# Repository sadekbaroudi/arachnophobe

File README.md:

# arachnophobe

A 30 key column staggered board using the Seeed RP2040. Uses kailh hotswap and supports both Choc v1 and MX switches on the same pcb.

# Support me!

I have spent a lot of time and money designing prototypes, testing, developing, etc. Any contributions would be greatly appreciated!

If you don't want to, or can't afford to support me, please send me a message to let me know you've built one, along with pictures. Also, feel free to submit a pull request with pictures into this repository. I'd be happy to showcase your build.

Reddit: /u/sadekbaroudi
Discord: sadekbaroudi#1258

# Keymap

# Firmware

## QMK
[arachnophobe-qmk](https://github.com/sadekbaroudi/qmk_firmware/tree/master/keyboards/fingerpunch/arachnophobe)

Note that you may need to copy this folder into the latest develop branch (as of this writing, 2022-07-13) to get the RP2040 support in QMK.

## ZMK

[arachnophobe-zmk](https://github.com/sadekbaroudi/zmk-arachnophobe)

# Images

## PCB

## Choc build

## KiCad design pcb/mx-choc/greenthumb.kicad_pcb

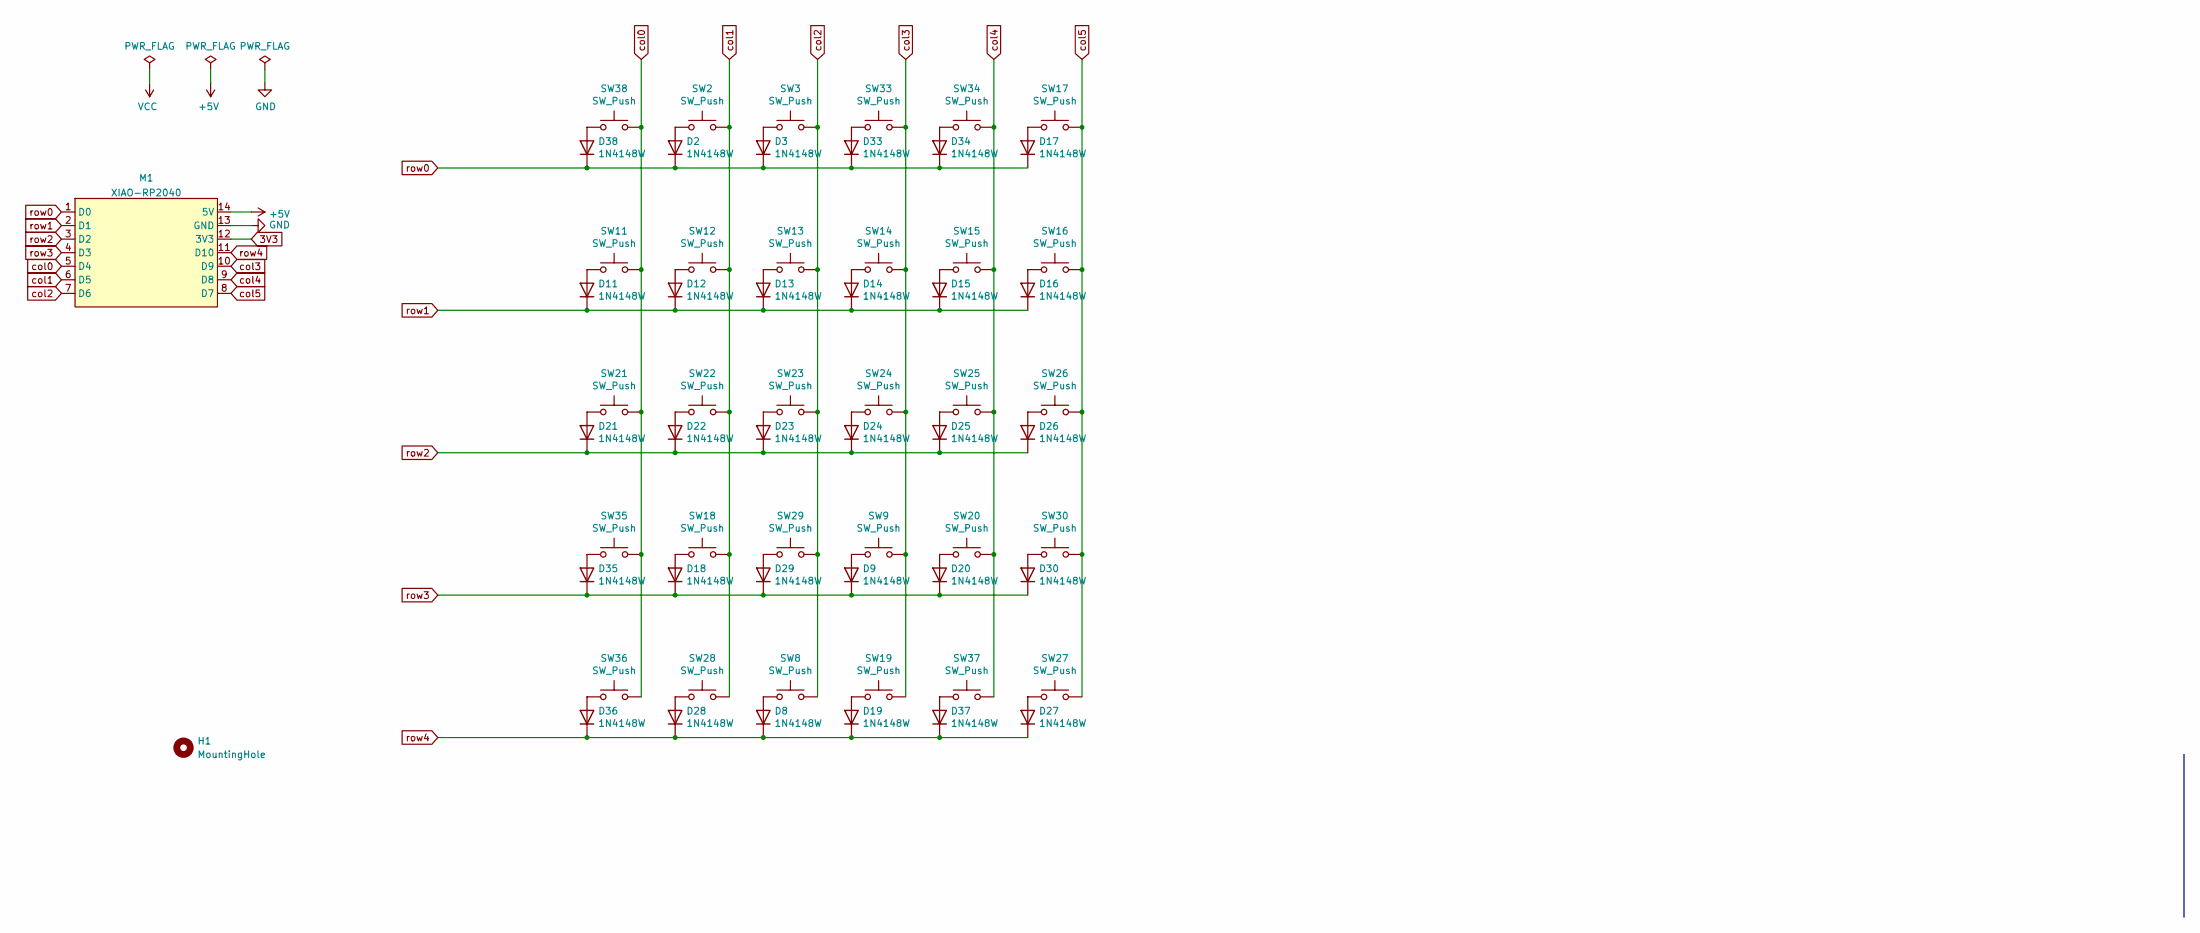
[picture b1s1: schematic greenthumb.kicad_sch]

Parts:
D2, D3, D8, D9, D11, D12, D13, D14, D15, D16, D17, D18, D19, D20, D21, D22, D23, D24, D25, D26, D27, D28, D29, D30, D33, D34, D35, D36, D37, D38: 1N4148W; D_SOD-123; LCSC C909967
H1: MountingHole; fingerpunch-logo
M1: XIAO-RP2040; LCSC 102010428
SW2, SW3, SW8, SW9, SW11, SW12, SW13, SW14, SW15, SW16, SW17, SW18, SW19, SW20, SW21, SW22, SW23, SW24, SW25, SW26, SW27, SW28, SW29, SW30, SW33, SW34, SW35, SW36, SW37, SW38: SW_Push; Kailh_socket_MX-ChocV1

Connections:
3V3: M1.12 (3V3)
+5V: M1.14 (5V)
GND: M1.13 (GND)
unnamed: D2.2 (A), SW2.1
unnamed: D3.2 (A), SW3.1
unnamed: D8.2 (A), SW8.1
unnamed: D9.2 (A), SW9.1
unnamed: D11.2 (A), SW11.1
unnamed: D12.2 (A), SW12.1
unnamed: D13.2 (A), SW13.1
unnamed: D14.2 (A), SW14.1
unnamed: D15.2 (A), SW15.1
unnamed: D16.2 (A), SW16.1
unnamed: D17.2 (A), SW17.1
unnamed: D18.2 (A), SW18.1
unnamed: D19.2 (A), SW19.1
unnamed: D20.2 (A), SW20.1
unnamed: D21.2 (A), SW21.1
unnamed: D22.2 (A), SW22.1
unnamed: D23.2 (A), SW23.1
unnamed: D24.2 (A), SW24.1
unnamed: D25.2 (A), SW25.1
unnamed: D26.2 (A), SW26.1
unnamed: D27.2 (A), SW27.1
unnamed: D28.2 (A), SW28.1
unnamed: D29.2 (A), SW29.1
unnamed: D30.2 (A), SW30.1
unnamed: D33.2 (A), SW33.1
unnamed: D34.2 (A), SW34.1
unnamed: D35.2 (A), SW35.1
unnamed: D36.2 (A), SW36.1
unnamed: D37.2 (A), SW37.1
unnamed: D38.2 (A), SW38.1
col0: M1.5 (D4), SW11.2, SW21.2, SW35.2, SW36.2, SW38.2
col1: M1.6 (D5), SW2.2, SW12.2, SW18.2, SW22.2, SW28.2
col2: M1.7 (D6), SW3.2, SW8.2, SW13.2, SW23.2, SW29.2
col3: M1.10 (D9), SW9.2, SW14.2, SW19.2, SW24.2, SW33.2
col4: M1.9 (D8), SW15.2, SW20.2, SW25.2, SW34.2, SW37.2
col5: M1.8 (D7), SW16.2, SW17.2, SW26.2, SW27.2, SW30.2
row0: D2.1 (K), D3.1 (K), D17.1 (K), D33.1 (K), D34.1 (K), D38.1 (K), M1.1 (D0)
row1: D11.1 (K), D12.1 (K), D13.1 (K), D14.1 (K), D15.1 (K), D16.1 (K), M1.2 (D1)
row2: D21.1 (K), D22.1 (K), D23.1 (K), D24.1 (K), D25.1 (K), D26.1 (K), M1.3 (D2)
row3: D9.1 (K), D18.1 (K), D20.1 (K), D29.1 (K), D30.1 (K), D35.1 (K), M1.4 (D3)
row4: D8.1 (K), D19.1 (K), D27.1 (K), D28.1 (K), D36.1 (K), D37.1 (K), M1.11 (D10)

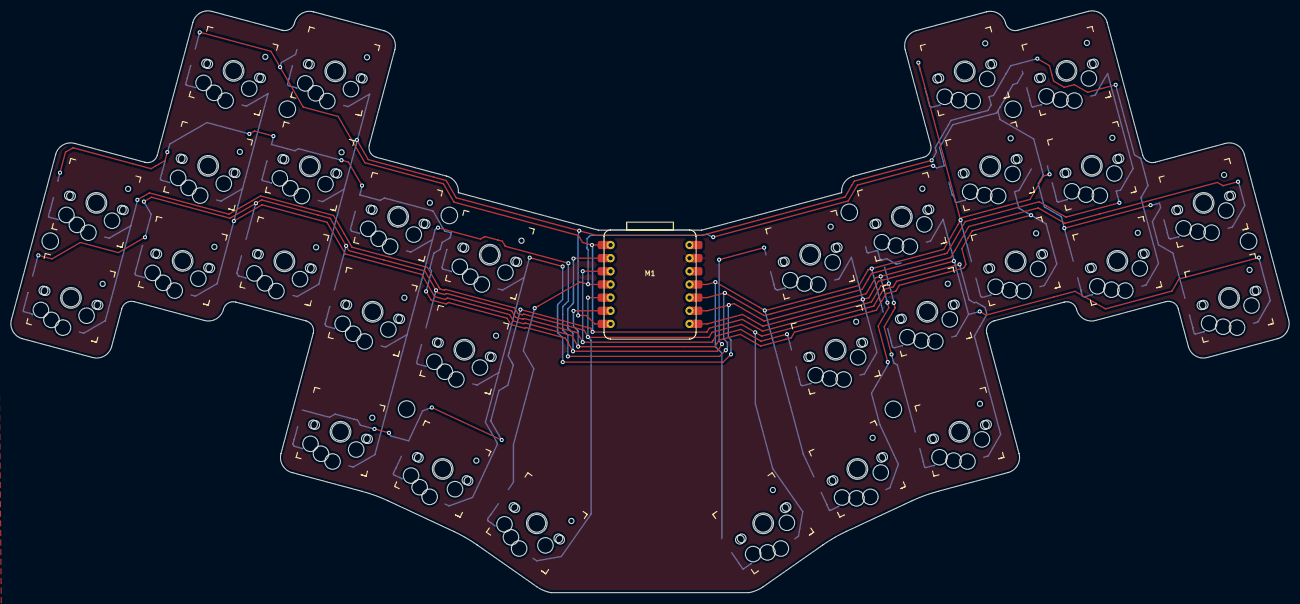
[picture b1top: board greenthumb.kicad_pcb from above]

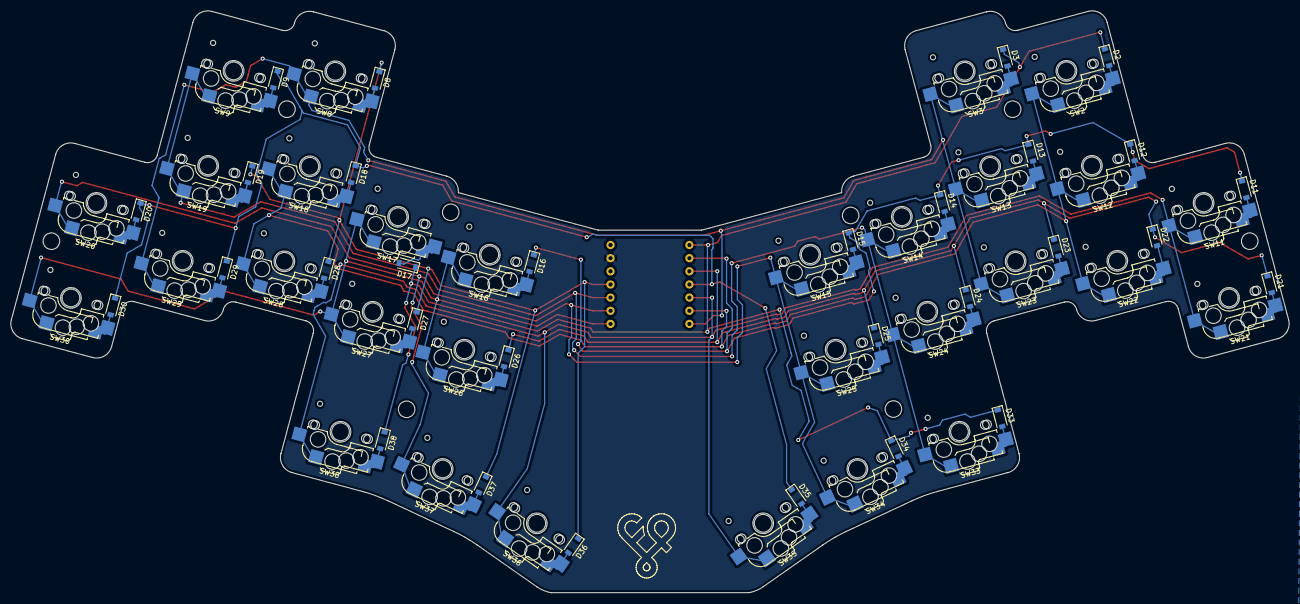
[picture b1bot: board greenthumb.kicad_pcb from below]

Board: 2 copper layers, 246.9 x 112.4 mm, 62 parts (31 on the bottom side), 41 nets.

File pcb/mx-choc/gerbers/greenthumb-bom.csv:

Comment,Designator,Footprint,LCSC
"1N4148W","D2,D3,D8,D9,D11,D12,D13,D14,D15,D16,D17,D18,D19,D20,D21,D22,D23,D24,D25,D26,D27,D28,D29,D30,D33,D34,D35,D36,D37,D38","Diode_SMD:D_SOD-123","C909967"
"MountingHole","H1","fingerpunch:fingerpunch-logo",""
"XIAO-RP2040","M1","fingerpunch:XIAO-RP2040","102010428"
"SW_Push","SW2,SW3,SW8,SW9,SW11,SW12,SW13,SW14,SW15,SW16,SW17,SW18,SW19,SW20,SW21,SW22,SW23,SW24,SW25,SW26,SW27,SW28,SW29,SW30,SW33,SW34,SW35,SW36,SW37,SW38","fingerpunch:Kailh_socket_MX-ChocV1",""

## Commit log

2022-06-11 first commit, pcb just needs routing
2022-06-12 routing almost done
2022-06-13 completed pcb
2022-07-11 cleaned up some extra files, fixed fingerpunch logo orientation, moved reset switch to bottom of pcb
2022-07-11 arachnophobe case
2022-07-12 moved the gap out a bit for the reset switch, added mx case
2022-07-12 choc case rename
2022-07-13 added readme and images
2022-07-16 removed reset switch, as it wasn't being used, and no way to hook it up to the seeeduino
2022-08-05 added keymap image
2022-10-10 layout tester
